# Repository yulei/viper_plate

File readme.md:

# Plate for the viper or eagle keyboard

This plate uses 8 [rgb leds](https://item.szlcsc.com/391391.html) to replace the 
indicator leds on the original viper/eagle pcb.

Two [TM1812](https://item.szlcsc.com/62468.html) were used to drive those leds. The 
protocol of TM1812 was almost the same as the WS2812 family, thus it's easy to integrate
with commonly avaibly GH60 boards such as the DP60.

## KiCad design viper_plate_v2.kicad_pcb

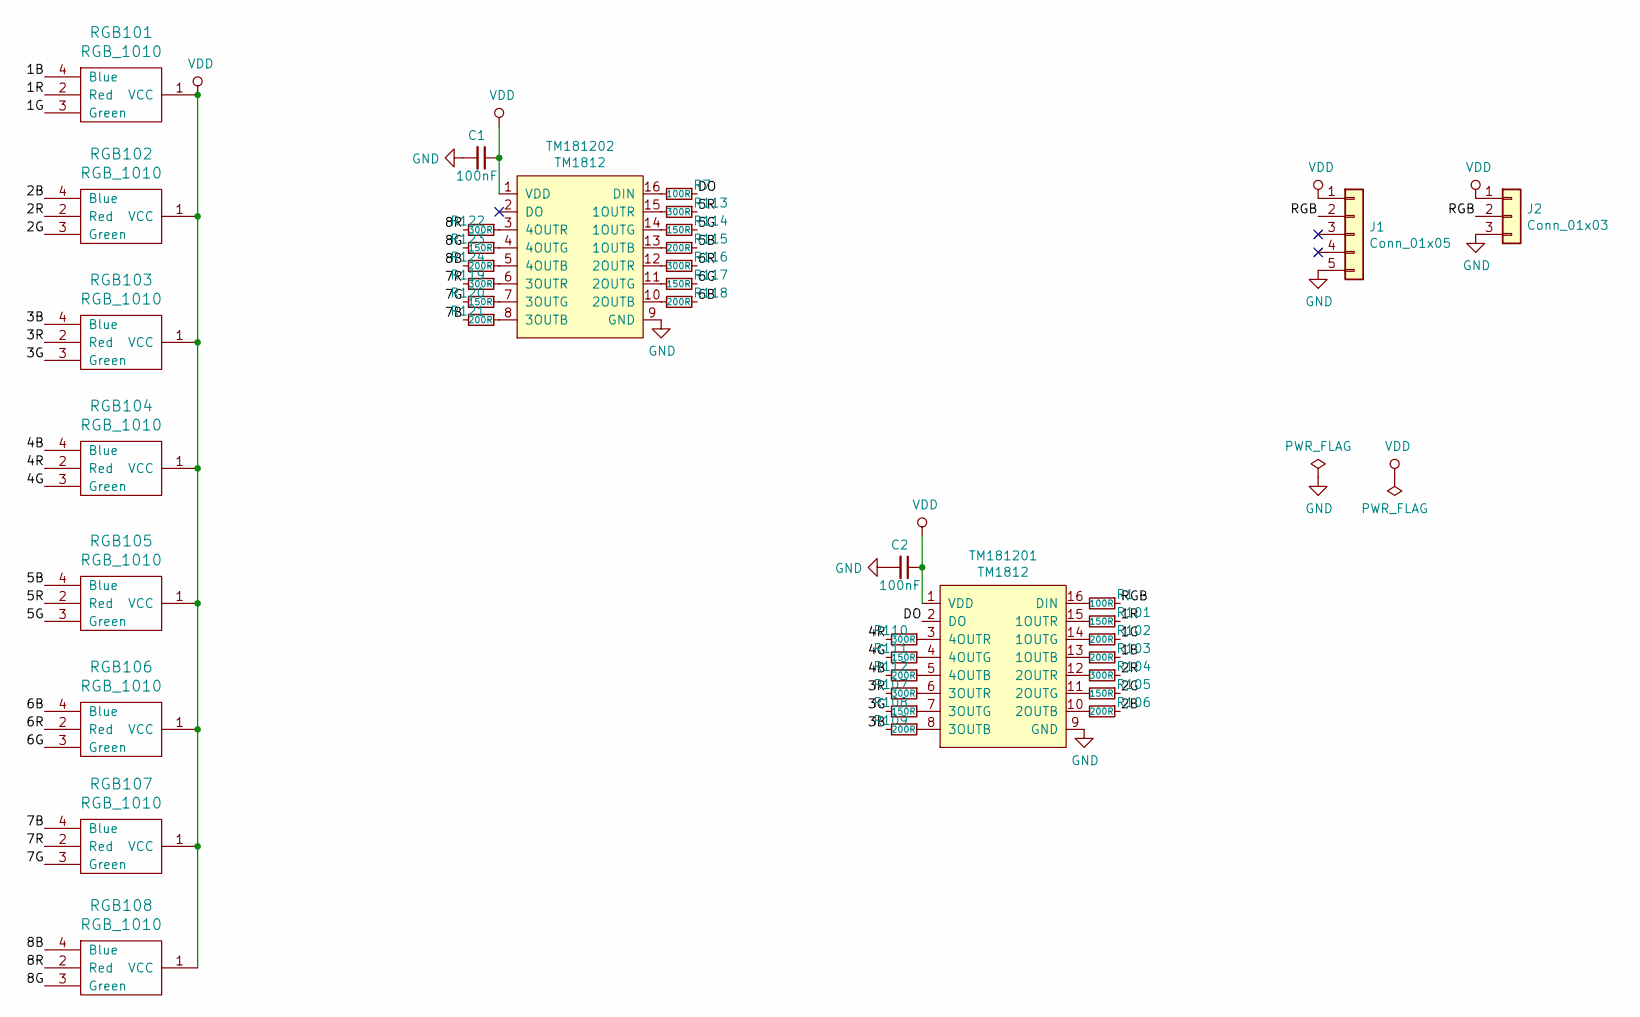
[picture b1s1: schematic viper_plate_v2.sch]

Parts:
C1, C2: 100nF; C_0603_1608Metric
J1: Conn_01x05; PinHeader_1x05_P1.27mm_Horizontal
J2: Conn_01x03; PinHeader_1x03_P2.54mm_Vertical
R1, R7: 100R; R_0402_1005Metric
R101, R105, R108, R111, R114, R117, R120, R123: 150R; R_0402_1005Metric
R102, R103, R106, R109, R112, R115, R118, R121, R124: 200R; R_0402_1005Metric
R104, R107, R110, R113, R116, R119, R122: 300R; R_0402_1005Metric
RGB101, RGB102, RGB103, RGB104, RGB105, RGB106, RGB107, RGB108: RGB_1010; LED_RGB_1515
TM181201, TM181202: TM1812; TM1812_SOP-16_4x10mm_P1.27mm_

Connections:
/1B: R103.1, RGB101.4 (Blue)
/1G: R102.1, RGB101.3 (Green)
/1R: R101.1, RGB101.2 (Red)
/2B: R106.1, RGB102.4 (Blue)
/2G: R105.1, RGB102.3 (Green)
/2R: R104.1, RGB102.2 (Red)
/3B: R109.2, RGB103.4 (Blue)
/3G: R108.2, RGB103.3 (Green)
/3R: R107.2, RGB103.2 (Red)
/4B: R112.2, RGB104.4 (Blue)
/4G: R111.2, RGB104.3 (Green)
/4R: R110.2, RGB104.2 (Red)
/5B: R115.1, RGB105.4 (Blue)
/5G: R114.1, RGB105.3 (Green)
/5R: R113.1, RGB105.2 (Red)
/6B: R118.1, RGB106.4 (Blue)
/6G: R117.1, RGB106.3 (Green)
/6R: R116.1, RGB106.2 (Red)
/7B: R121.2, RGB107.4 (Blue)
/7G: R120.2, RGB107.3 (Green)
/7R: R119.2, RGB107.2 (Red)
/8B: R124.2, RGB108.4 (Blue)
/8G: R123.2, RGB108.3 (Green)
/8R: R122.2, RGB108.2 (Red)
/DO: R7.1, TM181201.2 (DO)
/RGB: J1.2, J2.2, R1.1
GND: C1.2, C2.2, J1.5, J2.3, TM181201.9 (GND), TM181202.9 (GND)
unnamed: R1.2, TM181201.16 (DIN)
unnamed: R7.2, TM181202.16 (DIN)
unnamed: R101.2, TM181201.15 (1OUTR)
unnamed: R102.2, TM181201.14 (1OUTG)
unnamed: R103.2, TM181201.13 (1OUTB)
unnamed: R104.2, TM181201.12 (2OUTR)
unnamed: R105.2, TM181201.11 (2OUTG)
unnamed: R106.2, TM181201.10 (2OUTB)
unnamed: R107.1, TM181201.6 (3OUTR)
unnamed: R108.1, TM181201.7 (3OUTG)
unnamed: R109.1, TM181201.8 (3OUTB)
unnamed: R110.1, TM181201.3 (4OUTR)
unnamed: R111.1, TM181201.4 (4OUTG)
unnamed: R112.1, TM181201.5 (4OUTB)
unnamed: R113.2, TM181202.15 (1OUTR)
unnamed: R114.2, TM181202.14 (1OUTG)
unnamed: R115.2, TM181202.13 (1OUTB)
unnamed: R116.2, TM181202.12 (2OUTR)
unnamed: R117.2, TM181202.11 (2OUTG)
unnamed: R118.2, TM181202.10 (2OUTB)
unnamed: R119.1, TM181202.6 (3OUTR)
unnamed: R120.1, TM181202.7 (3OUTG)
unnamed: R121.1, TM181202.8 (3OUTB)
unnamed: R122.1, TM181202.3 (4OUTR)
unnamed: R123.1, TM181202.4 (4OUTG)
unnamed: R124.1, TM181202.5 (4OUTB)
VDD: C1.1, C2.1, J1.1, J2.1, RGB101.1 (VCC), RGB102.1 (VCC), RGB103.1 (VCC), RGB104.1 (VCC), RGB105.1 (VCC), RGB106.1 (VCC), RGB107.1 (VCC), RGB108.1 (VCC), TM181201.1 (VDD), TM181202.1 (VDD)

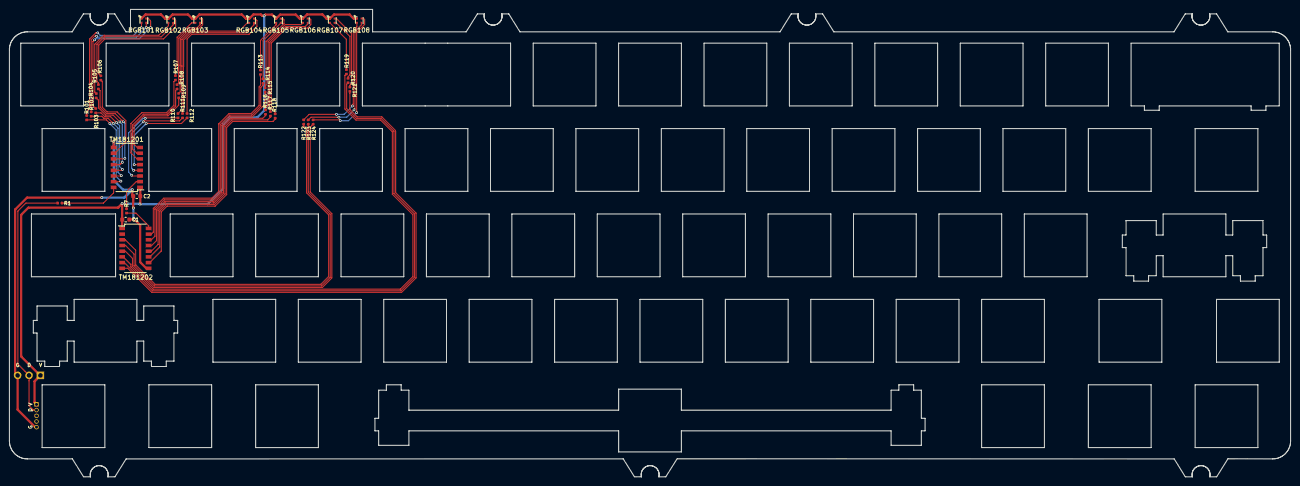
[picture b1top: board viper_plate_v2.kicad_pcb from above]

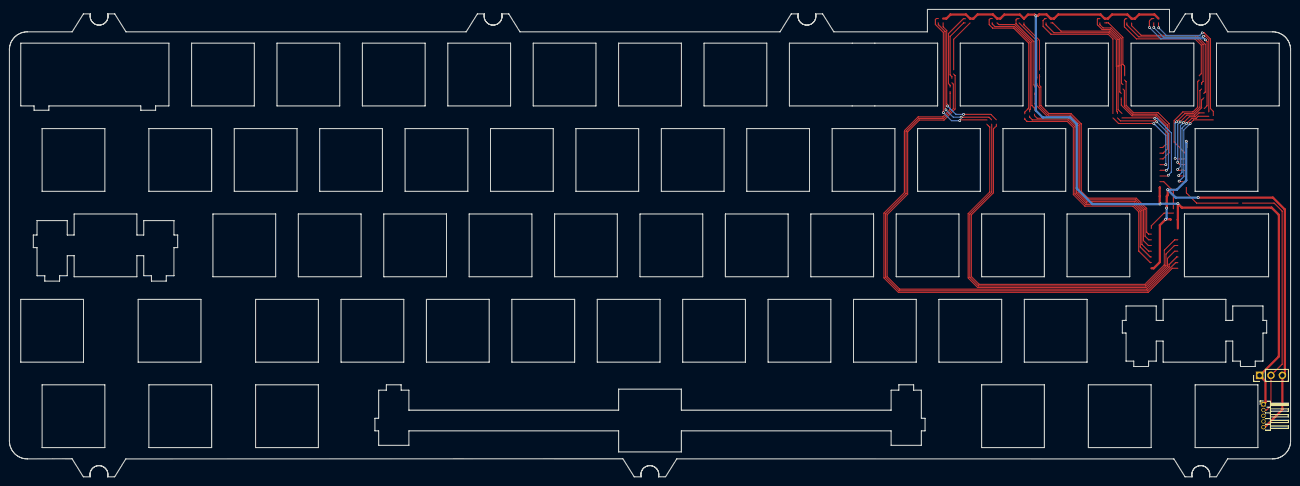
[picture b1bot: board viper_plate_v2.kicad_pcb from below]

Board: 2 copper layers, 285.8 x 104.3 mm, 40 parts (2 on the bottom side), 54 nets.

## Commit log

2020-04-14 made it public
2020-04-14 add plate image
